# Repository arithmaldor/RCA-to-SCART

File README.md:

# Copyright and Disclaimer
Copyright: Jacob Proctor 2018

This documentation describes Open Hardware and is licensed under the
CERN OHL v. 1.2.

You may redistribute and modify this documentation under the terms of the
CERN OHL v.1.2. (http://ohwr.org/cernohl). This documentation is distributed
WITHOUT ANY EXPRESS OR IMPLIED WARRANTY, INCLUDING OF
MERCHANTABILITY, SATISFACTORY QUALITY AND FITNESS FOR A
PARTICULAR PURPOSE. Please see the CERN OHL v.1.2 for applicable
conditions

# RCA to SCART Board

Output version of the SCART to RCA board. This one has optional sync attentuation via a jumper (closed to bypass resistor footprint) and
optional power input via microusb for TVs that automatically switch to SCART (just leave the usb and 100 ohm resistor footprints blank if you
don't need this).

# Parts

SCART Connector: K-SCARTX-024, available on Mouser

RCA Connector: PJRAS3X2S01 is available on Mouser and Digikey, but the colors are wrong. Here are the ones I used, a bit cheaper per part:

https://www.ebay.com/itm/QTY-10-6-WAY-PCB-FEMALE-RCA-JACKS-GREEN-YELLOW-BLUE-WHITE-RED-RED-RCA-268N1-14/112220720415?var=null

microusb port: Molex 105017-0001

Resistors: 0805 size, 470 ohm for sync attenuation, 100 ohm for dividing the voltage for RGB and TV detect on pins 8 and 16. Just about any decent
quality ones will do.

Mounting hole size is M3, can be used with motherboard standoffs for mounting on MDF or acrylic or something else.

# Changelog
0.1 - This board is untested, I may be a few soon after which I will update the version number to 1.0 if everything works out.

0.2 - The shield througholes of the microusb port were not connected to ground, this has been fixed. I also moved a few traces
around to make it easier to disconnect pin 8 if it is causing your TV to force to 16:9.

# OSHPark
https://oshpark.com/shared_projects/9mo0B0iU

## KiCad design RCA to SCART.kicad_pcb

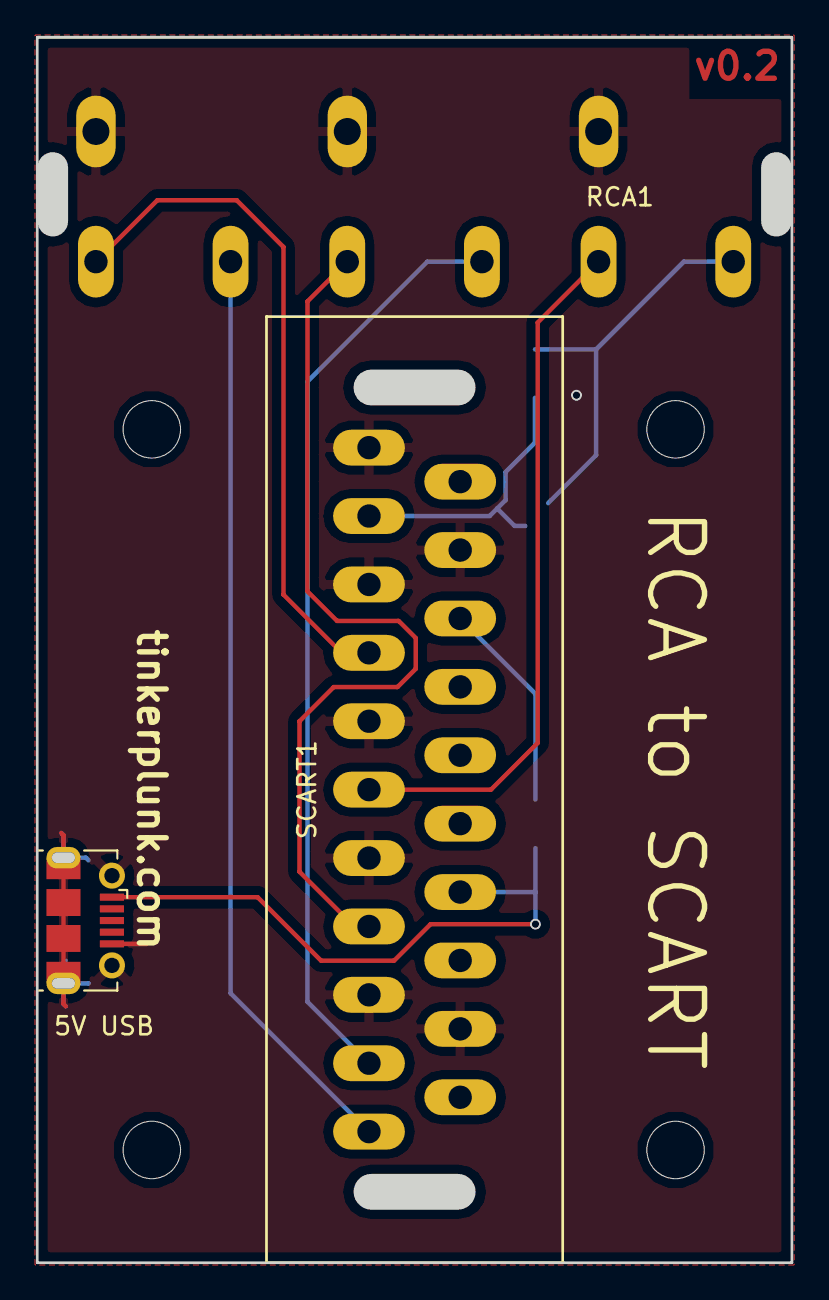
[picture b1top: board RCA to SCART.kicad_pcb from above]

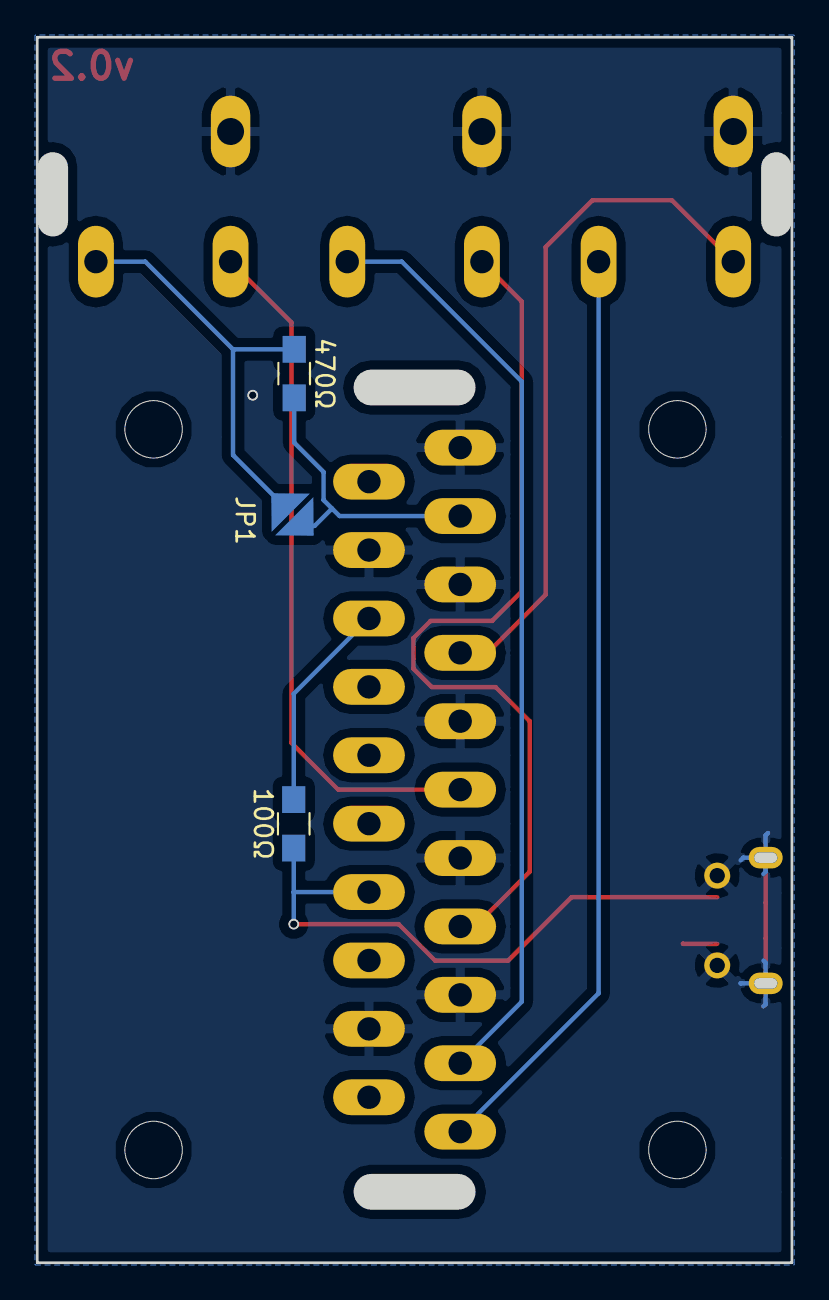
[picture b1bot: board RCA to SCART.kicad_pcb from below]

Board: 2 copper layers, 40.2 x 66.4 mm, 10 parts (3 on the bottom side), 10 nets.

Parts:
5V USB: Conn_Coaxial_Power; USB_Micro-B_Molex-105017-0001
100Ω: 100; R_0805_HandSoldering
470Ω: R; R_0805_HandSoldering
J1, J2, J3, J4: Conn_01x01; MountingHole_3.2mm_M3
JP1: Jumper_NO_Small; Jumper
RCA1: 3x2_RCA
SCART1: SCART-F; SCART_F

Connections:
BLUE: RCA1.4, SCART1.7
GND: 5V USB.5, 5V USB.6, RCA1.7, RCA1.8, RCA1.9, SCART1.4, SCART1.5, SCART1.9, SCART1.13, SCART1.17, SCART1.18, SCART1.21
GREEN: RCA1.2, SCART1.11
L_AUD: RCA1.3, SCART1.3
unnamed: 5V USB.1, 100Ω.1, SCART1.8
unnamed: 470Ω.1, JP1.2, RCA1.1
unnamed: 100Ω.2, SCART1.16
RED: RCA1.6, SCART1.15
R_AUD: RCA1.5, SCART1.1
SYNC: 470Ω.2, JP1.1, SCART1.19

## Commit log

2018-06-11 v0.2
    0.2 - The shield througholes of the microusb port were not connected to ground, this has been fixed. I also moved a few traces
    around to make it easier to disconnect pin 8 if it is causing your TV to force to 16:9.
2018-06-11 readme
    updated readme
2018-06-11 oshpark link
    changed link to updated oshpark page
